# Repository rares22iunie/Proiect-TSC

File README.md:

# OpenBook eBook Reader
Acest proiect reprezintă un cititor de eBook-uri portabil, cu consum redus de energie, afișaj E-Ink și conectivitate modernă, proiectat în jurul microcontrollerului ESP32-C6-WROOM-1-N8.

# Arhitectură hardware
- Microcontroller – ESP32-C6-WROOM-1-N8
- Procesor RISC-V

- Conectivitate: Wi-Fi 6 și Bluetooth 5

- Suport criptografie hardware

- Flash extern NOR de 64MB (W25Q512JVEIQ), conectat pe magistrală SPI dedicată

Interfețe: SPI, I2C, GPIO

## Sistem de alimentare
- Conector USB-C (PMF0501) – intrare standard 5V

- Protecție ESD pentru liniile USB (USBLC6-2SC6Y)

- Circuit de încărcare Li-Po (MCP73831), max. 500 mA

- Baterie Li-Po 3.7V

- Regulator LDO 3.3V (MCP1700-3302E) pentru alimentarea circuitelor

## Afișaj E-Ink
- Conector compatibil cu ecrane E-Paper de 1.54” (200x200 px)

- Circuit dedicat de generare a tensiunii (tranzistor, inductor, diodă)

- Jumper selector pentru tipul de ecran (SJ1)

- Interfață SPI + pini GPIO pentru control, conectat la ESP32-C6

## Memorie externă
- Card SD (SPI) pentru stocarea fișierelor eBook

- Memorie NOR Flash de 64MB (W25Q512JVEIQ) pentru resurse firmware (fonturi, imagini)

## Senzori și periferice
- BME688 – senzor de temperatură, umiditate, presiune, compuși volatili (I2C)

- DS3231SN – modul RTC de precizie (I2C)

- MAX17048G-T10 – monitorizare baterie (fuel gauge, I2C)

- Butoane pentru reset și boot (GPIO)

- Conector Qwiic / Stemma QT pentru extensii rapide I2C
# Block Diagram

# Design PCB și carcasă
- Placă PCB organizată în blocuri funcționale: alimentare, MCU, afișaj, senzori

- Trasee optimizate și plan de masă comun

- Protecții ESD incluse

- Conectori externi ușor accesibili (USB, butoane, display)

- Randări 3D disponibile

- Carcasă 3D compactă și ergonomică, gata de printare/turnare

# Conexiuni ESP32-C6
| Componenta     | Interfata  | Pini ESP32-C6                      | Observatii                    |
|----------------|------------|------------------------------------|-------------------------------|
| SD Card        | SPI        | GPIO10, GPIO11, GPIO12, GPIO13     | Bus SPI pentru card SD        |
| NOR Flash      | SPI        | GPIO6, GPIO7, GPIO8, GPIO9         | Bus SPI separat               |
| E-Ink Display  | SPI + GPIO | GPIO18, GPIO19, GPIO20, GPIO21     | Control display si date       |
| BME688         | I2C        | GPIO1 (SDA), GPIO2 (SCL)           | Bus comun I2C                 |
| DS3231         | I2C        | GPIO1 (SDA), GPIO2 (SCL)           | Comun cu ceilalti senzori     |
| MAX17048       | I2C        | GPIO1 (SDA), GPIO2 (SCL)           | Comun cu ceilalti senzori     |
| Butoane        | GPIO       | GPIO0 (RST), GPIO3 (BOOT)          | Control de sistem             |
| Test Pads      | GPIO/UART  | GPIO17, GPIO22                     | Debug                         |
| Stemma/Qwiic   | I2C        | GPIO1 (SDA), GPIO2 (SCL)           | Extensii rapide               |

# Estimare consum de energie
| Modul                  | Consum mediu        |
|------------------------|---------------------|
| ESP32-C6 activ         | ~80-100 mA          |
| ESP32-C6 deep sleep    | ~10 uA              |
| E-Ink refresh          | ~25 mA (temporar)   |
| SD Card (idle/acces)   | ~2 mA / ~50 mA      |
| RTC + BME688 standby   | ~3-5 uA             |
| MAX17048               | ~3 uA               |

**Durata estimata cu baterie 500mAh:**

- Utilizare activă: 15–20 ore

- Standby (deep sleep): până la câteva săptămâni

# Bill of Materials

| Cantitate | Componentă                         | Valoare | Descriere                                 | Carcasă                         | Reper        | Link Cumpărare                                                                 | Datasheet                                                                          |
|-----------|------------------------------------|---------|-------------------------------------------|---------------------------------|--------------|----------------------------------------------------------------------------------|------------------------------------------------------------------------------------|
| 1         | ADAFRUIT_LEDCHIP-LED0603           | -       | LED                                       | ADAFRUIT_CHIP-LED0603           | CHG_LED      | [link](https://www.mouser.com/ProductDetail/Adafruit/CHIP-LED0603)               | [datasheet](https://www.mouser.com/datasheet/2/737/CHIP-LED0603-1877199.pdf)       |
| 1         | SJ                                 | -       | SMD solder JUMPER                         | SJ                              | SJ1          | [link](https://www.mouser.com/ProductDetail/TE-Connectivity/1-2176091-2)         | [datasheet](https://www.mouser.com/datasheet/2/418/1-2176091-2-1817091.pdf)        |
| 1         | ESP32_WROVER_EAGLE-LTSPICE_RR0402  | 0.47Ω   | Rezistor                                  | ESP32_WROVER_EAGLE-LTSPICE_R0402| R3           | [link](https://www.mouser.com/ProductDetail/Vishay/CRCW04020047ZRT7)             | [datasheet](https://www.mouser.com/datasheet/2/427/crcwce-1764191.pdf)             |
| 1         | ESP32_WROVER_EAGLE-LTSPICE_RR0402  | 100KΩ   | Rezistor                                  | ESP32_WROVER_EAGLE-LTSPICE_R0402| R1_PWRUSB    | [link](https://www.mouser.com/ProductDetail/Vishay/CRCW0402100KFKED)             | [datasheet](https://www.mouser.com/datasheet/2/427/crcwce-1764191.pdf)             |
| 8         | EAGLE-LTSPICE_CC0402               | 100nF   | Condensator                               | EAGLE-LTSPICE_C0402             | C1, C2, C4_USB, C6, C8, C9, C10, C_DELAY | [link](https://www.mouser.com/ProductDetail/Murata/GRM155R71C104KA88D)            | [datasheet](https://www.mouser.com/datasheet/2/281/GRM155R71C104KA88D-1767201.pdf) |
| 1         | RCL_CPOL-EUCT3528                  | 100µF   | Condensator polarizat                     | RCL_CT3528                      | C3           | [link](https://www.mouser.com/ProductDetail/Panasonic/EEE-FK1V101P)              | [datasheet](https://www.mouser.com/datasheet/2/315/EEE-FK1V101P-1526881.pdf)       |
| 10        | ESP32_WROVER_EAGLE-LTSPICE_RR0402  | 10KΩ    | Rezistor                                  | ESP32_WROVER_EAGLE-LTSPICE_R0402| R1, R1-PINH, R1_PINH1, R2-PINH, R2_PINH1, R4, R_BOOT, R_CHANGE, R_CL1, R_RESET | [link](https://www.mouser.com/ProductDetail/Vishay/CRCW040210K0FKED)              | [datasheet](https://www.mouser.com/datasheet/2/427/crcwce-1764191.pdf)             |
| 6         | ESP32_WROVER_EAGLE-LTSPICE_RR0402  | 10kΩ    | Rezistor                                  | ESP32_WROVER_EAGLE-LTSPICE_R0402| R5, R6, R7, R8, R9, R10 | [link](https://www.mouser.com/ProductDetail/Vishay/CRCW040210K0FKED)              | [datasheet](https://www.mouser.com/datasheet/2/427/crcwce-1764191.pdf)             |
| 1         | EAGLE-LTSPICE_CC0402               | 10µF    | Condensator                               | EAGLE-LTSPICE_C0402             | C7           | [link](https://www.mouser.com/ProductDetail/Murata/GRM155R61A106ME44D)           | [datasheet](https://www.mouser.com/datasheet/2/281/GRM155R61A106ME44D-1767201.pdf) |
| 1         | 112A-TAAR-R03_ATTEND               | -       | Micro SD Card Socket, Push-Push Type      | 112ATAARR03ATTEND               | J4           | [link](https://www.mouser.com/ProductDetail/Attend/112A-TAAR-R03)                | [datasheet](https://www.mouser.com/datasheet/2/828/112A-TAAR-R03-1222862.pdf)      |
| 1         | ESP32_WROVER_EAGLE-LTSPICE_RR0402  | 15Ω     | Rezistor                                  | ESP32_WROVER_EAGLE-LTSPICE_R0402| R_CAPACITOR  | [link](https://www.mouser.com/ProductDetail/Vishay/CRCW040215R0FKED)             | [datasheet](https://www.mouser.com/datasheet/2/427/crcwce-1764191.pdf)             |
| 1         | EAGLE-LTSPICE_CC0402               | 1µF     | Condensator                               | EAGLE-LTSPICE_C0402             | C5           | [link](https://www.mouser.com/ProductDetail/Murata/GRM155R61A105KE15D)           | [datasheet](https://www.mouser.com/datasheet/2/281/GRM155R61A105KE15D-1767201.pdf) |
| 10        | EAGLE-LTSPICE_CC0402               | 1µF/50V | Condensator ceramic multi-strat           | 0402                           | EPD_C1, EPD_C2, EPD_C5, EPD_C6, EPD_C7, EPD_C8, EPD_C9, EPD_C10, EPD_C11, EPD_C12 | [link](https://www.mouser.com/ProductDetail/Murata-Electronics/GRM155R61A105KE15D) | [datasheet](https://www.mouser.com/datasheet/2/281/1/GRM155R61A105KE15_01A-1983730.pdf) |

# Aplicații posibile
- eBook Reader offline

- Afișaj de birou cu date locale (calendar, vreme, informații personale)

- Platformă portabilă pentru aplicații IoT low-power

# Resurse
- Documentație oficială ESP32-C6: https://www.espressif.com/en/products/modules/esp32-c6

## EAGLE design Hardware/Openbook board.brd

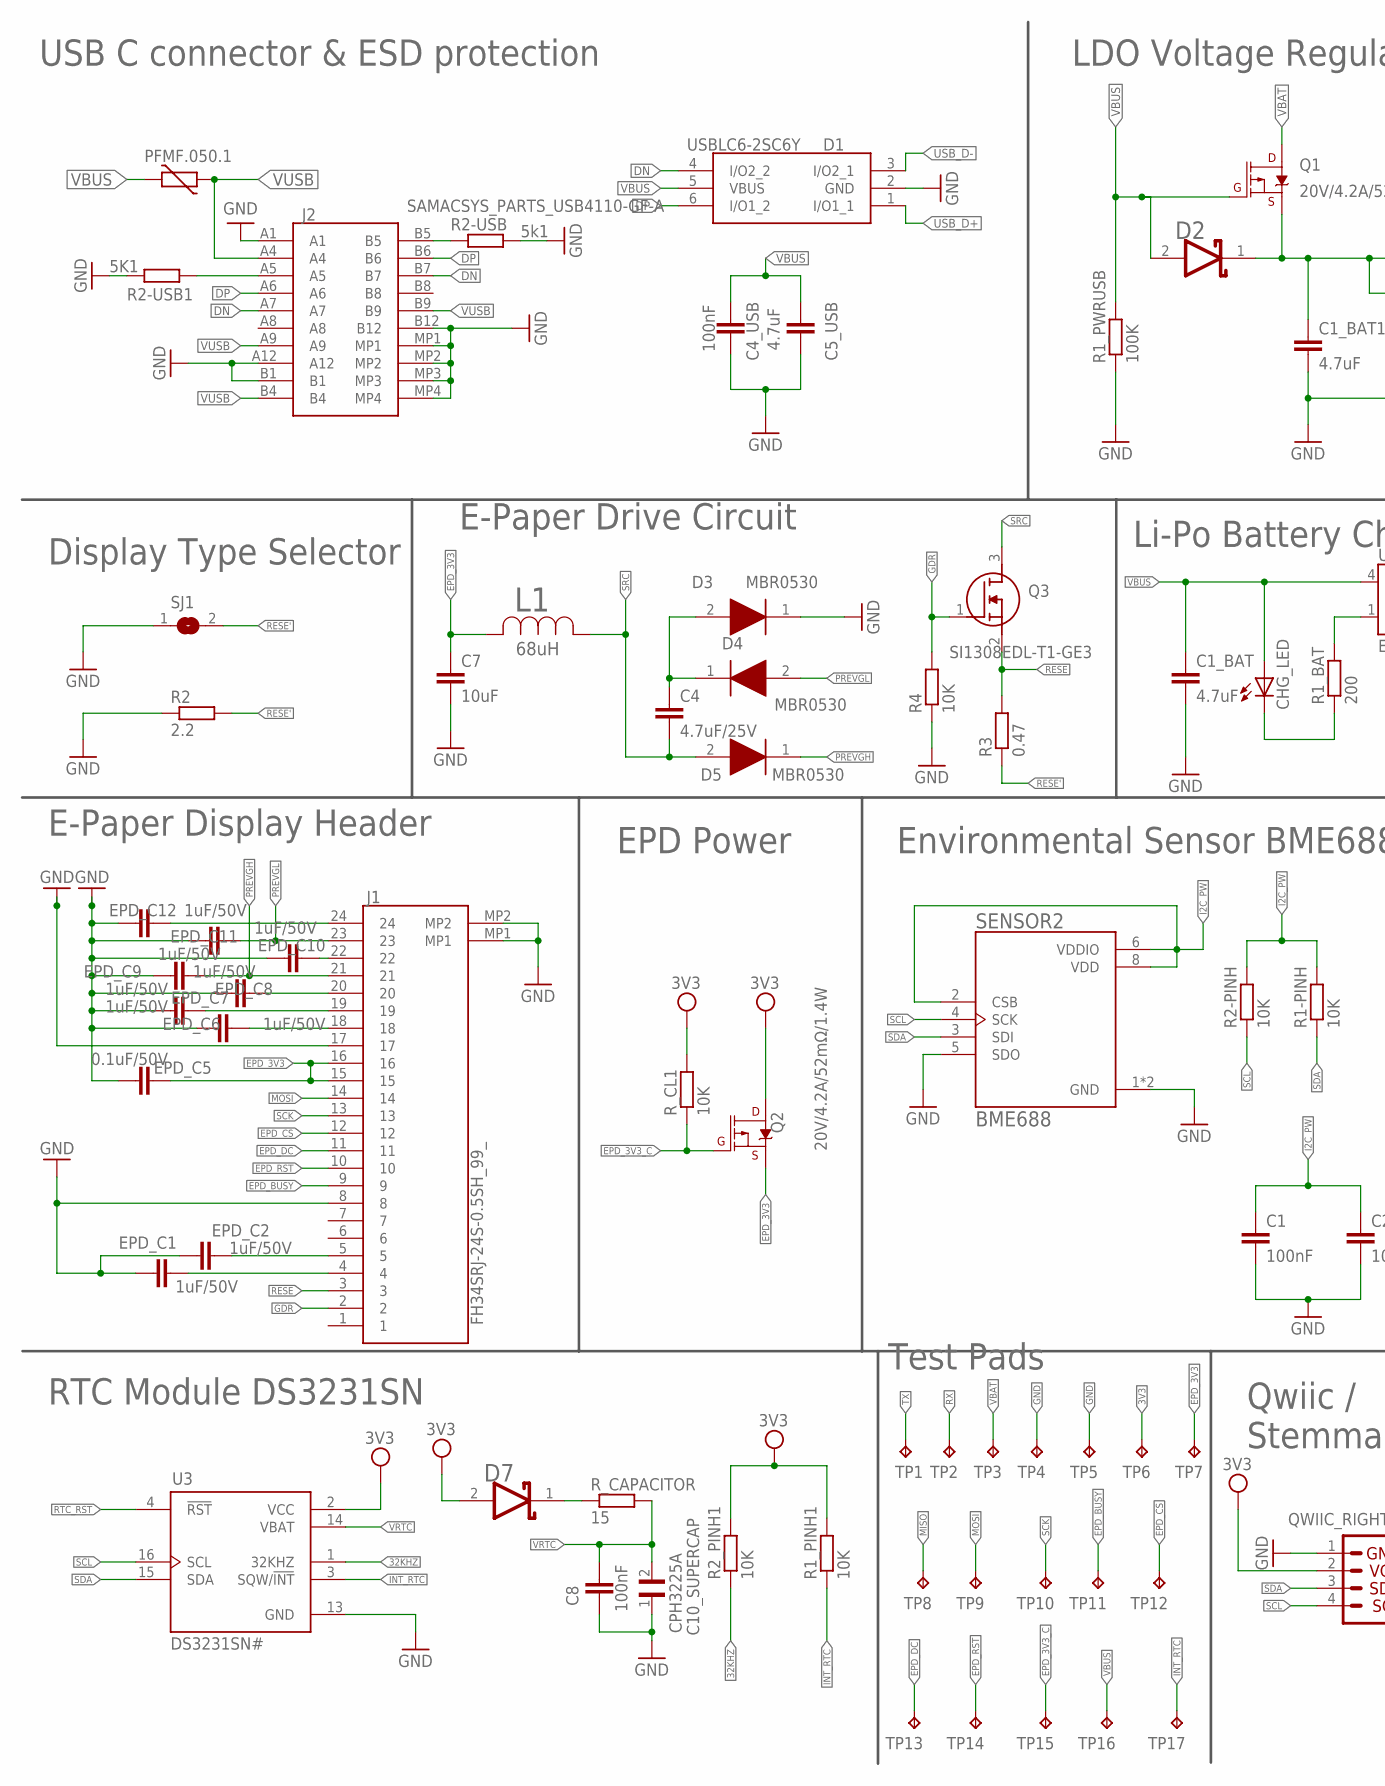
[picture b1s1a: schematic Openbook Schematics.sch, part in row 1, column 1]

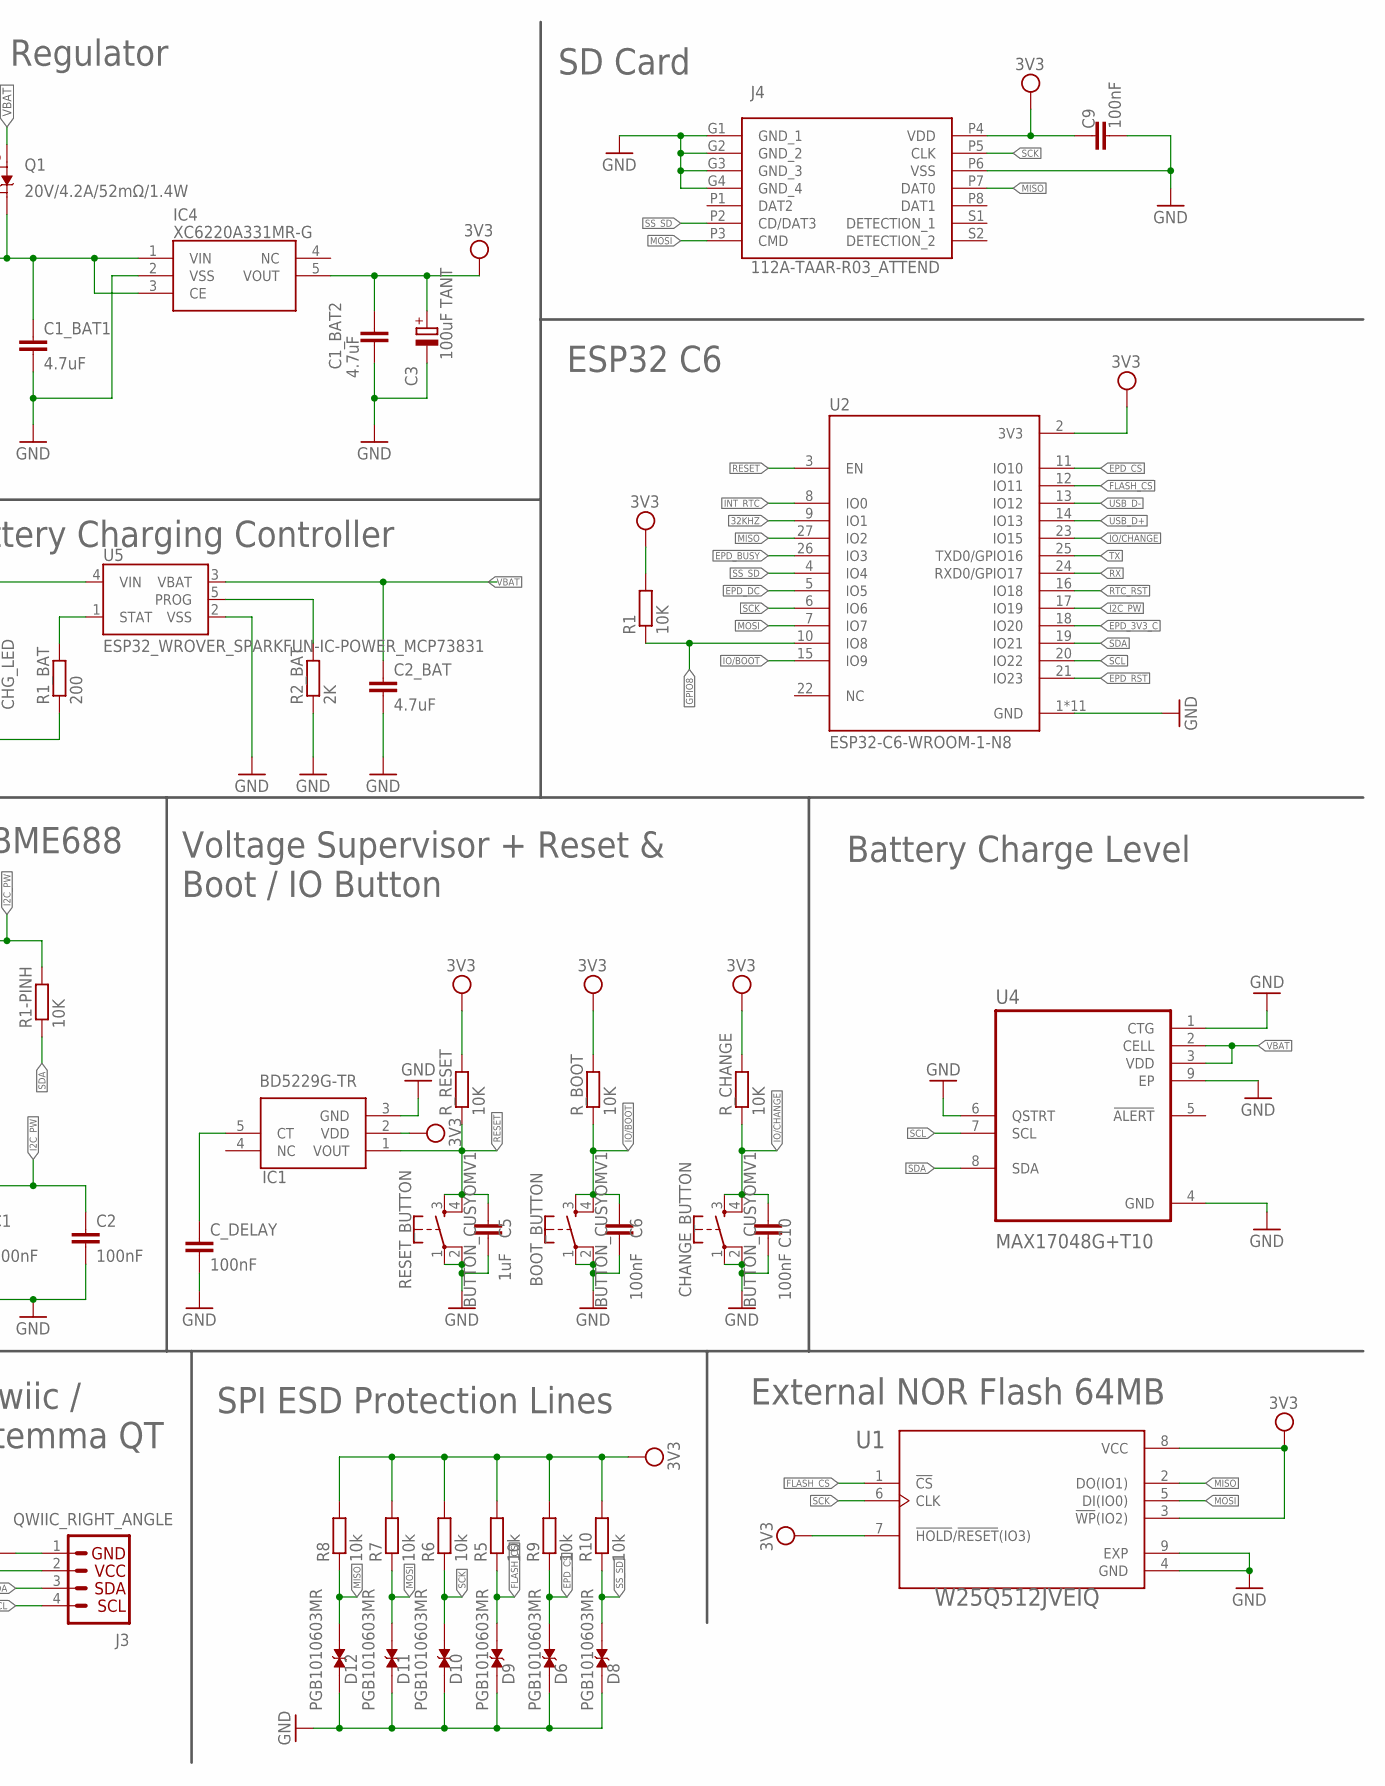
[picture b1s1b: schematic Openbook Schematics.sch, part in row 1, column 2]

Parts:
BOOT_BUTTON: BUTTON_CUSYOMV1; MYBUTTON
C1, C2, C4_USB, C6, C8, C9, C10: 100nF; EAGLE-LTSPICE_C0402
C1_BAT, C1_BAT2, C2_BAT, C5_USB: 4.7uF; EAGLE-LTSPICE_C0402
C1_BAT1: 4.7uF; ESP32_WROVER_EAGLE-LTSPICE_C0402
C3: 100uF TANT; RCL_CT3528
C4: 4.7uF/25V; EAGLE-LTSPICE_C0402
C5: 1uF; EAGLE-LTSPICE_C0402
C7: 10uF; EAGLE-LTSPICE_C0402
C10_SUPERCAP: CPH3225A; CAPCP3225X100N
CHANGE_BUTTON: BUTTON_CUSYOMV1; MYBUTTON
CHG_LED: ADAFRUIT_LEDCHIP-LED0603; ADAFRUIT_CHIP-LED0603
C_DELAY: 100nF; EAGLE-LTSPICE_C0402
D1: USBLC6-2SC6Y; SOT95P280X145-6N
D2, D7: ESP32_WROVER_AVX---SD0805S020S1R0_AVX_SD0805S020S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; ESP32_WROVER_AVX---SD0805S020S1R0_AVX_SD0805S020S1R0_0
D3, D4, D5: MBR0530; SOD3716X135N
D6, D8, D9, D10, D11, D12: PGB1010603MR; DIOC1608X36N
EPD_C1, EPD_C2, EPD_C6, EPD_C7, EPD_C8, EPD_C9, EPD_C10, EPD_C11, EPD_C12: 1uF/50V; EAGLE-LTSPICE_C0402
EPD_C5: 0.1uF/50V; EAGLE-LTSPICE_C0402
IC1: BD5229G-TR; SOT95P280X125-5N
IC4: XC6220A331MR-G; SOT95P280X120-5N
J1: FH34SRJ-24S-0.5SH_99_; FH34SRJ24S05SH99
J2: SAMACSYS_PARTS_USB4110-GF-A; SAMACSYS_PARTS_USB4110GFA
J3: QWIIC_RIGHT_ANGLE; JST04_1MM_RA
J4: 112A-TAAR-R03_ATTEND; 112ATAARR03ATTEND
L1: 68uH; IND_4828-WE-TPC_WRE
PFMF.050.1: ESP32C6_VARISTORCN1812; ESP32C6_VARISTOR_CT/CN1812
Q1, Q2: 20V/4.2A/52mΩ/1.4W; ESP32_WROVER_SPARKFUN-DISCRETESEMI_SOT23-3
Q3: SI1308EDL-T1-GE3; SOT65P210X110-3N
R1, R1-PINH, R1_PINH1, R2-PINH, R2_PINH1, R4: 10K; ESP32_WROVER_EAGLE-LTSPICE_R0402
R1_BAT: 200; ESP32_WROVER_EAGLE-LTSPICE_R0402
R1_PWRUSB: 100K; ESP32_WROVER_EAGLE-LTSPICE_R0402
R2: 2.2; ESP32_WROVER_EAGLE-LTSPICE_R0402
R2-USB: 5k1; ESP32_WROVER_EAGLE-LTSPICE_R0402
R2-USB1: 5K1; ESP32_WROVER_EAGLE-LTSPICE_R0402
R2_BAT: 2K; ESP32_WROVER_EAGLE-LTSPICE_R0402
R3: 0.47; ESP32_WROVER_EAGLE-LTSPICE_R0402
R5, R6, R7, R8, R9, R10: 10k; ESP32_WROVER_EAGLE-LTSPICE_R0402
RESET_BUTTON: BUTTON_CUSYOMV1; MYBUTTON
R_BOOT: 10K; ESP32_WROVER_EAGLE-LTSPICE_R0402
R_CAPACITOR: 15; ESP32_WROVER_EAGLE-LTSPICE_R0402
R_CHANGE: 10K; ESP32_WROVER_EAGLE-LTSPICE_R0402
R_CL1: 10K; ESP32_WROVER_EAGLE-LTSPICE_R0402
R_RESET: 10K; ESP32_WROVER_EAGLE-LTSPICE_R0402
SENSOR2: BME688; ESP32_WROVER_BME680_PSON80P300X300X100-8N
SJ1: SJ
TP1, TP2, TP3, TP4, TP5, TP6, TP7, TP8, TP9, TP10, TP11, TP12, TP13, TP14, TP15, TP16, TP17: TPTP20R; TP20R
U1: W25Q512JVEIQ; SON127P600X800X80-9N
U2: ESP32-C6-WROOM-1-N8; XCVR_ESP32-C6-WROOM-1-N8
U3: DS3231SN#; SOIC127P1032X265-16N
U4: MAX17048G+T10; SON50P200X200X80-9N
U5: ESP32_WROVER_SPARKFUN-IC-POWER_MCP73831; ESP32_WROVER_SPARKFUN-IC-POWER_SOT23-5

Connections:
3V3: C1_BAT2.1, C3.+, C9.2, D7.2 (ANODE), IC1.2 (VDD), IC4.5 (VOUT), J3.2, J4.P4 (VDD), Q2.3 (D), R1.2, R1_PINH1.2, R2_PINH1.2, R5.2, R6.2, R7.2, R8.2, R9.2, R10.2, R_BOOT.2, R_CHANGE.2, R_CL1.2, R_RESET.2, TP6.TP, U1.3 (!WP!(IO2)), U1.7 (!HOLD!/!RESET!(IO3)), U1.8 (VCC), U2.2 (3V3), U3.2 (VCC)
32KHZ: R2_PINH1.1, U2.9 (IO1), U3.1 (32KHZ)
DN: D1.4 (I/O2_2), J2.A7, J2.B7
DP: D1.6 (I/O1_2), J2.A6, J2.B6
EPD_3V3: C7.1, EPD_C5.2, J1.15, J1.16, L1.2, Q2.2 (S), TP7.TP
EPD_3V3_C: Q2.1 (G), R_CL1.1, TP15.TP, U2.18 (IO20)
EPD_BUSY: J1.9, TP11.TP, U2.26 (IO3)
EPD_CS: D6.2, J1.12, R9.1, TP12.TP, U2.11 (IO10)
EPD_DC: J1.11, TP13.TP, U2.5 (IO5)
EPD_RST: J1.10, TP14.TP, U2.21 (IO23)
FLASH_CS: D9.2, R5.1, U1.1 (!CS), U2.12 (IO11)
GDR: J1.2, Q3.1 (G), R4.2
GND: BOOT_BUTTON.1, BOOT_BUTTON.2, C1.2, C1_BAT.2, C1_BAT1.2, C1_BAT2.2, C2.2, C2_BAT.2, C3.-, C4_USB.2, C5.2, C5_USB.2, C6.2, C7.2, C8.2, C9.1, C10.2, C10_SUPERCAP.1, CHANGE_BUTTON.1, CHANGE_BUTTON.2, C_DELAY.2, D1.2 (GND), D3.1 (K), D6.1, D8.1, D9.1, D10.1, D11.1, D12.1, EPD_C1.1, EPD_C2.1, EPD_C5.1, EPD_C6.1, EPD_C7.1, EPD_C8.1, EPD_C9.1, EPD_C10.1, EPD_C11.1, EPD_C12.1, IC1.3 (GND), IC4.2 (VSS), J1.8, J1.17, J1.MP1, J1.MP2, J2.A1, J2.A12, J2.B1, J2.B12, J2.MP1, J2.MP2, J2.MP3, J2.MP4, J3.1, J4.G1 (GND_1), J4.G2 (GND_2), J4.G3 (GND_3), J4.G4 (GND_4), J4.P6 (VSS), R1_PWRUSB.1, R2.1, R2-USB.2, R2-USB1.1, R2_BAT.1, R4.1, RESET_BUTTON.1, RESET_BUTTON.2, SENSOR2.1 (GND), SENSOR2.5 (SDO), SENSOR2.7 (GND), SJ1.1, TP4.TP, TP5.TP, U1.4 (GND), U1.9 (EXP), U2.1 (GND), U2.28 (GND), U2.29_1 (GND), U2.29_2 (GND), U2.29_3 (GND), U2.29_4 (GND), U2.29_5 (GND), U2.29_6 (GND), U2.29_7 (GND), U2.29_8 (GND), U2.29_9 (GND), U3.13 (GND), U4.1 (CTG), U4.4 (GND), U4.6 (QSTRT), U4.9 (EP), U5.2 (VSS)
GPIO8: R1.1, U2.10 (IO8)
I2C_PW: C1.1, C2.1, R1-PINH.2, R2-PINH.2, SENSOR2.2 (CSB), SENSOR2.6 (VDDIO), SENSOR2.8 (VDD), U2.17 (IO19)
INT_RTC: R1_PINH1.1, TP17.TP, U2.8 (IO0), U3.3 (SQW/!INT)
IO/BOOT: BOOT_BUTTON.3, BOOT_BUTTON.4, C6.1, R_BOOT.1, U2.15 (IO9)
IO/CHANGE: C10.1, CHANGE_BUTTON.3, CHANGE_BUTTON.4, R_CHANGE.1, U2.23 (IO15)
MISO: D12.2, J4.P7 (DAT0), R8.1, TP8.TP, U1.2 (DO(IO1)), U2.27 (IO2)
MOSI: D11.2, J1.14, J4.P3 (CMD), R7.1, TP9.TP, U1.5 (DI(IO0)), U2.7 (IO7)
unnamed: J2.A5, R2-USB1.2
unnamed: J2.B5, R2-USB.1
unnamed: C_DELAY.1, IC1.5 (CT)
unnamed: R1_BAT.2, U5.1 (STAT)
unnamed: C1_BAT1.1, D2.1 (CATHODE), IC4.1 (VIN), IC4.3 (CE), Q1.2 (S)
unnamed: C4.1, D3.2 (A), D4.1 (K)
unnamed: CHG_LED.C, R1_BAT.1
unnamed: R2_BAT.2, U5.5 (PROG)
unnamed: EPD_C12.2, J1.24
unnamed: EPD_C10.2, J1.22
unnamed: EPD_C8.2, J1.20
unnamed: EPD_C7.2, J1.19
unnamed: EPD_C6.2, J1.18
unnamed: EPD_C2.2, J1.5
unnamed: EPD_C1.2, J1.4
unnamed: D7.1 (CATHODE), R_CAPACITOR.1
PREVGH: D5.1 (K), EPD_C9.2, J1.21
PREVGL: D4.2 (A), EPD_C11.2, J1.23
RESE: J1.3, Q3.2 (S), R3.2
RESE': R2.2, R3.1, SJ1.2
RESET: C5.1, IC1.1 (VOUT), RESET_BUTTON.3, RESET_BUTTON.4, R_RESET.1, U2.3 (EN)
RTC_RST: U2.16 (IO18), U3.4 (!RST)
RX: TP2.TP, U2.24 (RXD0/GPIO17)
SCK: D10.2, J1.13, J4.P5 (CLK), R6.1, TP10.TP, U1.6 (CLK), U2.6 (IO6)
SCL: J3.4, R2-PINH.1, SENSOR2.4 (SCK), U2.20 (IO22), U3.16 (SCL), U4.7 (SCL)
SDA: J3.3, R1-PINH.1, SENSOR2.3 (SDI), U2.19 (IO21), U3.15 (SDA), U4.8 (SDA)
SRC: C4.2, D5.2 (A), L1.1, Q3.3 (D)
SS_SD: D8.2, J4.P2 (CD/DAT3), R10.1, U2.4 (IO4)
TX: TP1.TP, U2.25 (TXD0/GPIO16)
USB_D+: D1.1 (I/O1_1), U2.14 (IO13)
USB_D-: D1.3 (I/O2_1), U2.13 (IO12)
VBAT: C2_BAT.1, Q1.3 (D), TP3.TP, U4.2 (CELL), U4.3 (VDD), U5.3 (VBAT)
VBUS: C1_BAT.1, C4_USB.1, C5_USB.1, CHG_LED.A, D1.5 (VBUS), D2.2 (ANODE), PFMF.050.1.2, Q1.1 (G), R1_PWRUSB.2, TP16.TP, U5.4 (VIN)
VRTC: C8.1, C10_SUPERCAP.2, R_CAPACITOR.2, U3.14 (VBAT)
VUSB: J2.A4, J2.A9, J2.B4, J2.B9, PFMF.050.1.1

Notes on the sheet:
USB C connector & ESD protection
LDO Voltage Regulator
SD Card
ESP32 C6
Display Type Selector
E-Paper Drive Circuit
Li-Po Battery Charging Controller
E-Paper Display Header
EPD Power
Environmental Sensor BME688
Voltage Supervisor + Reset & Boot / IO Button
Battery Charge Level
External NOR Flash 64MB
SPI ESD Protection Lines
Qwiic / Stemma QT
Test Pads
RTC Module DS3231SN

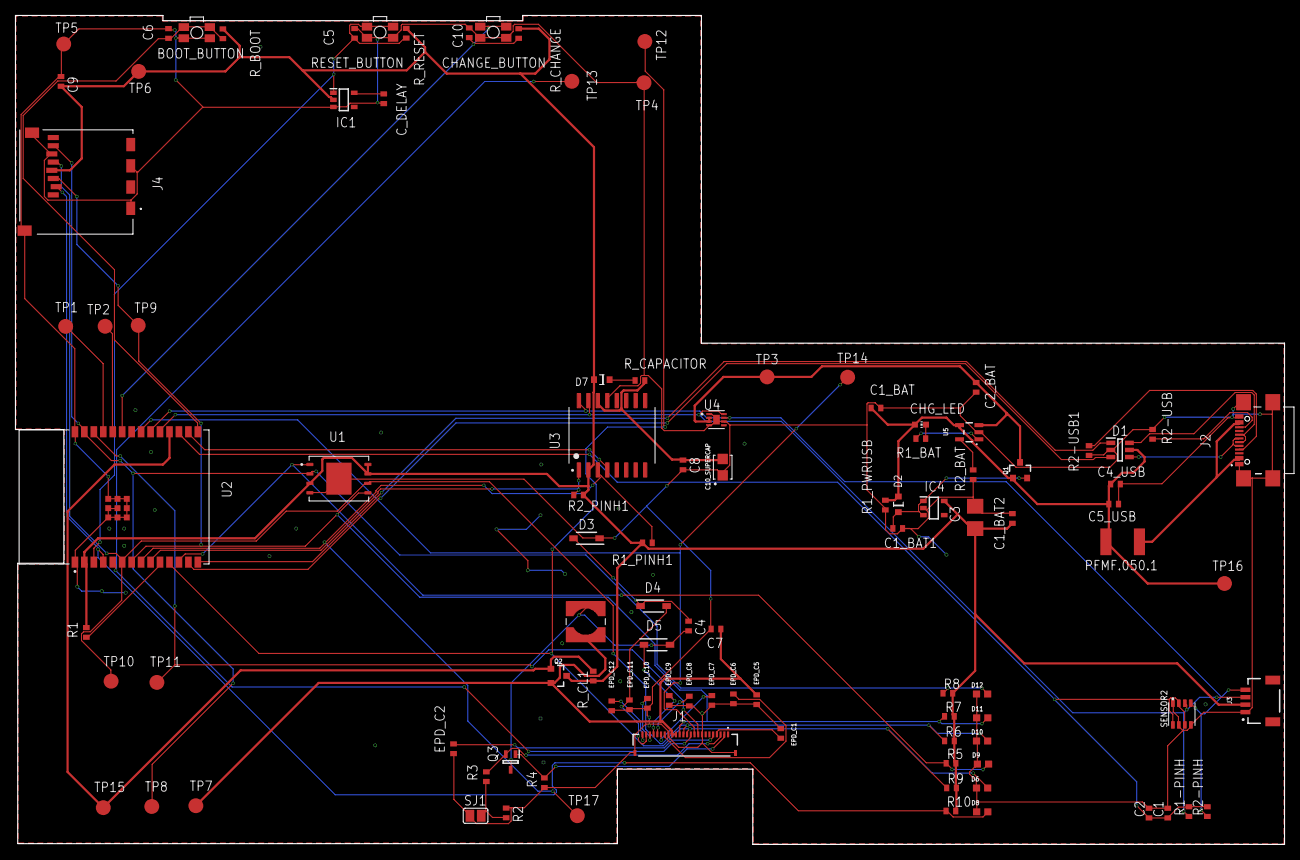
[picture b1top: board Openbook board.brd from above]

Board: 2 copper layers, 170.4 x 111.3 mm, 103 parts (0 on the bottom side), 55 nets.

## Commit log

2025-04-06 modify step to f3z
2025-04-06 Create LICENSE
2025-04-06 Images change
2025-04-14 Fix issues

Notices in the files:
parts and their libraries:
DeskAssistant v19 v1: COPYRIGHT: Copyright (C) 2024 Ultra Librarian. All rights reserved.
